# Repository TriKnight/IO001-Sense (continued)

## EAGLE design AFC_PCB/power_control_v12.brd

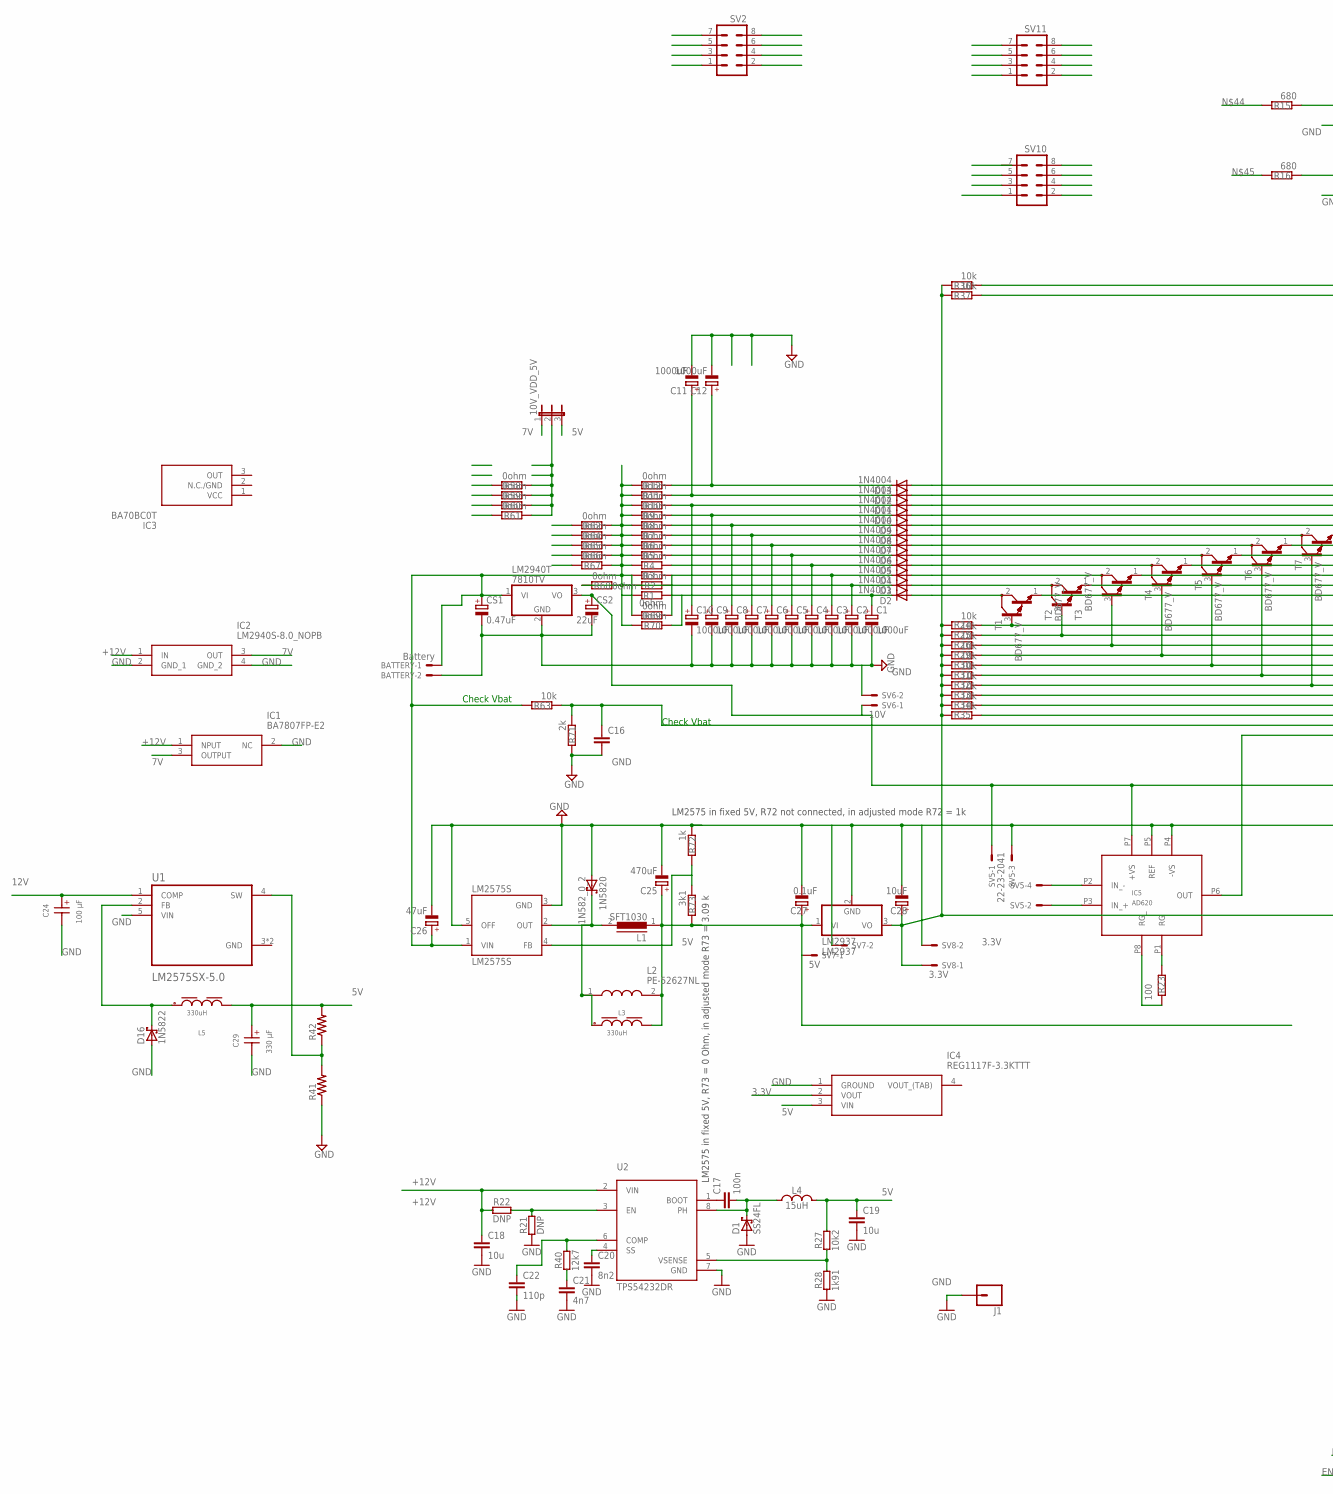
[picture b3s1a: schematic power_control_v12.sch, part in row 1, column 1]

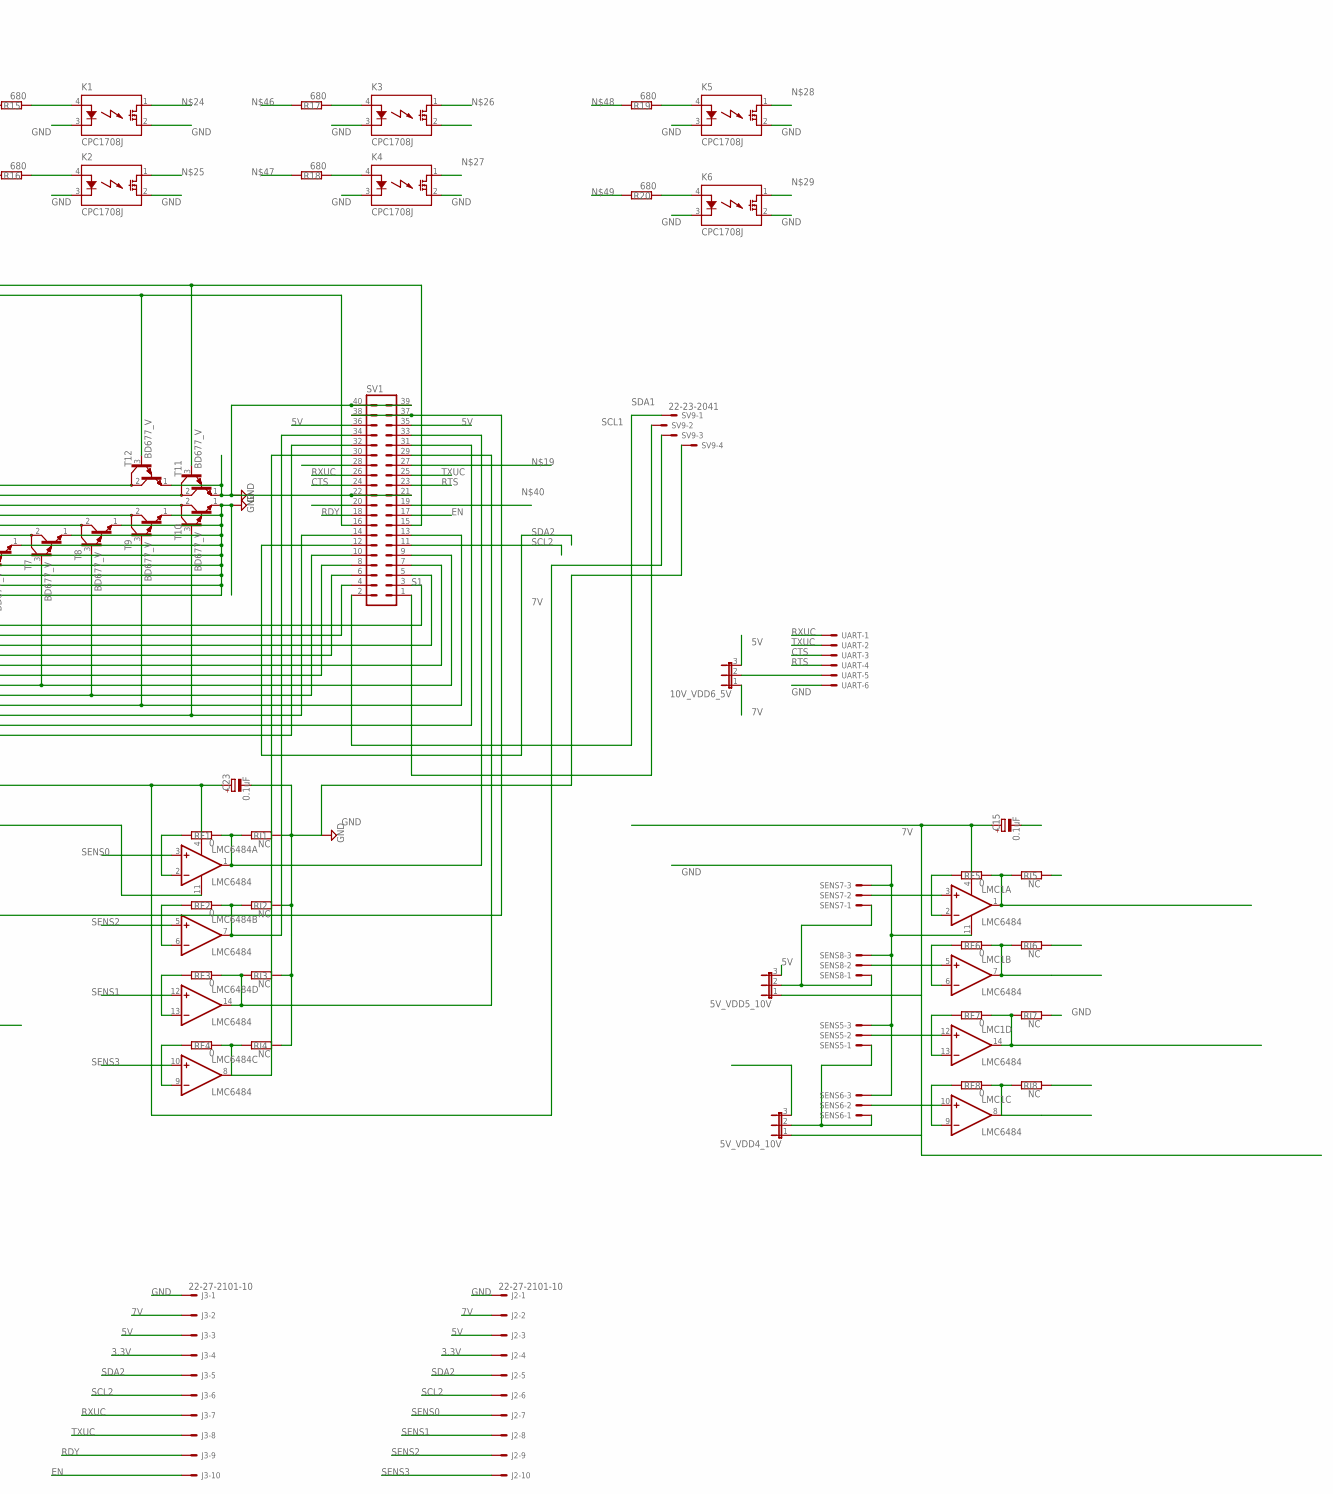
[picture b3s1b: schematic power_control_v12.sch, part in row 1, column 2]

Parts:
1N5820: 1N582_0_2; C4111-15
5V_VDD4_10V, 5V_VDD5_10V, 10V_VDD6_5V, 10V_VDD_5V: JP2E; JP2
BATTERY: Battery; 22-23-2021
C1, C2, C3, C4, C5, C6, C7, C8, C9, C10, C11, C12: 1000uF; E5-10,5
C15, C23, C27: 0.1uF; E1,8-4
C16: C-EUC0805K; C0805K
C17: 100n; 0402-1005X55N
C18, C19: 10u; 0603-1608X90N
C20: 8n2; 0402-1005X55N
C21: 4n7; 0402-1005X55N
C22: 110p; 0402-1005X55N
C24: 100 µF; WCAP-AS5H_10X10.5(DXL)
C25: 470uF; E3,5-8
C26: 47uF; E2-5
C28: 10uF; E1,8-4
C29: 330 µF; WCAP-AS5H_10X10.5(DXL)
CS1: 0.47uF; E2-5
CS2: 22uF; E2-5
D1: SS24FL; SOD123F
D2, D3: 1N4001; DO41-10
D4, D5, D6, D7, D8, D9, D10, D11, D12, D13: 1N4004; DO41-10
D16: 1N5822; C4111-15
IC1: BA7807FP-E2; BD33KA5FPE2
IC2: LM2940S-8.0_NOPB; KTT0003B
IC3: BA70BC0T; TO254P480X1010X2300-3P
IC4: REG1117F-3.3KTTT; TO254P1524X483-4N
IC5: AD620; DIL8
J1: CONN_01; 1X01
J2, J3: 22-27-2101-10; 6410-10
K1, K2, K3, K4, K5, K6: CPC1708J; I4-PAC
L1: SFT1030
L2: PE-52627NL; PE52629NL
L3, L5: 330uH; WE-PD_1280
L4: 15uH; SRN6045
LM2575S: LM2575S; TO263-5
LM2937: LM2937; TO263-3
LM2940T: 7810TV; TO220V
LMC1, LMC6484: LMC6484; DIL14
R1, R2, R3, R4, R5, R6, R7, R8, R9, R10, R11, R12: 0ohm; 0207/10
R15, R16, R17, R18, R19, R20: 680; M0805
R21, R22: DNP; 0402-1005X55N
R23: 100; R0805
R24, R25, R26, R29, R30, R31, R32, R33, R34, R35, R36, R37, R63: 10k; M0805
R27: 10k2; 0402-1005X55N
R28: 1k91; 0402-1005X55N
R40: 12k7; 0402-1005X55N
R41, R42: FLIPFLOP-RES; 0805-THM
R58, R59, R60, R61, R62, R64, R65, R66, R67, R68, R69, R70: 0ohm; M0805
R71: 2k; M0805
R72: 1k; M0805
R73: 3k1; M0805
RF1, RF3, RF4, RF5, RF7, RF8: 0; M0805
RF2, RF6: 0; R0805
RI1, RI2, RI3, RI4, RI5, RI6, RI7, RI8: NC; M0805
SENS5, SENS6, SENS7, SENS8: 22-23-2031
SV1: MA20-2
SV2, SV10, SV11: MA04-2
SV5, SV9: 22-23-2041
SV6: 10V; 22-23-2021
SV7: 5V; 22-23-2021
SV8: 3.3V; 22-23-2021
T1, T2, T3, T4, T5, T6, T7, T8, T9, T10, T11, T12: BD677_V; TO126V
U1: LM2575SX-5.0; VREG_TPS79625KTTR
U2: TPS54232DR; SO08
UART: 22-23-2061

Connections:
3.3V: C28.+, IC4.2 (VOUT), J2.4, J3.4, LM2937.3 (VO), R24.2, R25.2, R26.2, R29.2, R30.2, R31.2, R32.2, R33.2, R34.2, R35.2, R36.2, R37.2, SV1.37, SV1.38, SV8.1
5V: 5V_VDD4_10V.3, 5V_VDD5_10V.3, 10V_VDD6_5V.3, 10V_VDD_5V.3, C19.1, C25.+, C27.+, C29.1 (+), IC4.3 (VIN), J2.3, J3.3, L1.1, L2.2, L3.2, L4.2, L5.2, LM2937.1 (VI), R27.2, R42.2, R73.2, SV1.35, SV1.36, SV7.1
7V: 5V_VDD4_10V.1, 5V_VDD5_10V.1, 10V_VDD6_5V.1, 10V_VDD_5V.1, C15.+, C23.+, CS2.+, IC1.3 (OUTPUT), IC2.3 (OUT), IC5.P7 (+VS), J2.2, J3.2, LM2940T.3 (VO), LMC1.4 (V+), LMC6484.4 (V+), SV5.1, SV6.1, SV9.3
12V: C24.1 (+), U1.1 (COMP)
+12V: BATTERY.1, C18.1, C26.+, CS1.+, IC1.1 (NPUT), IC2.1 (IN), LM2575S.1 (VIN), LM2940T.1 (VI), R1.2, R2.2, R3.2, R4.2, R5.2, R6.2, R7.2, R8.2, R9.2, R10.2, R11.2, R12.2, R22.1, R62.1, R63.2, R64.1, R65.1, R66.1, R67.1, R68.1, R69.2, R70.2, U2.2 (VIN)
CTS: SV1.24, UART.3
EN: J3.10, SV1.17
GND: 1N5820.A, BATTERY.2, C1.-, C2.-, C3.-, C4.-, C5.-, C6.-, C7.-, C8.-, C9.-, C10.-, C11.-, C12.-, C15.-, C16.2, C18.2, C19.2, C20.2, C21.2, C22.2, C23.-, C24.2 (-), C25.-, C26.-, C27.-, C28.-, C29.2 (-), CS1.-, CS2.-, D1.A, D16.A, IC1.2 (NC), IC2.2 (GND_1), IC2.4 (GND_2), IC4.1 (GROUND), IC5.P4 (-VS), IC5.P5 (REF), J1.1, J2.1, J3.1, K1.2 (DS2), K1.3 (K), K2.2 (DS2), K2.3 (K), K3.2 (DS2), K3.3 (K), K4.2 (DS2), K4.3 (K), K5.2 (DS2), K5.3 (K), K6.2 (DS2), K6.3 (K), LM2575S.3 (GND), LM2575S.5 (OFF), LM2937.2 (GND), LM2940T.2 (GND), LMC1.11 (V-), LMC6484.11 (V-), R21.1, R28.1, R41.1, R71.2, R72.1, RI1.1, RI2.1, RI3.1, RI4.1, RI5.1, RI6.1, RI7.1, RI8.1, SENS5.3, SENS6.3, SENS7.3, SENS8.3, SV1.21, SV1.22, SV1.39, SV1.40, SV5.3, SV6.2, SV7.2, SV8.2, SV9.4, T1.1 (E), T2.1 (E), T3.1 (E), T4.1 (E), T5.1 (E), T6.1 (E), T7.1 (E), T8.1 (E), T9.1 (E), T10.1 (E), T11.1 (E), T12.1 (E), U1.3 (GND), U1.5 (VIN), U1.6 (GND), U2.7 (GND), UART.6
unnamed: C1.+, D2.C, R1.1, R70.1, SV2.1
unnamed: D2.A, SV2.2, T1.2 (C)
unnamed: C2.+, D3.C, R2.1, R68.2, SV2.3
unnamed: C3.+, D4.C, R3.1, R69.1, SV2.5
unnamed: C4.+, D5.C, R4.1, R67.2, SV2.7
unnamed: C5.+, D6.C, R5.1, R66.2, SV10.1
unnamed: C6.+, D7.C, R6.1, R65.2, SV10.3
unnamed: C7.+, D8.C, R7.1, R64.2, SV10.5
unnamed: C8.+, D9.C, R8.1, R62.2, SV10.7
unnamed: C9.+, D10.C, R9.1, R61.2, SV11.1
unnamed: C10.+, D11.C, R10.1, R60.2, SV11.3
unnamed: C11.+, D12.C, R11.1, R59.2, SV11.5
unnamed: C12.+, D13.C, R12.1, R58.2, SV11.7
unnamed: 5V_VDD4_10V.2, SENS5.1, SENS6.1
unnamed: LMC1.3 (+IN), SENS7.2
unnamed: LMC1.2 (-IN), RF5.2
unnamed: LMC1.1 (OUT), RF5.1, RI5.2, SV1.27
unnamed: 10V_VDD6_5V.2, UART.5
unnamed: LMC1.5 (+IN), SENS8.2
unnamed: LM2575S.4 (FB), R72.2, R73.1
unnamed: R36.1, SV1.15, T11.3 (B)
unnamed: D3.A, K1.1 (DS1), SV2.4, T2.2 (C)
unnamed: D4.A, K2.1 (DS1), SV2.6, T3.2 (C)
unnamed: D5.A, K3.1 (DS1), SV2.8, T4.2 (C)
unnamed: D6.A, K4.1 (DS1), SV10.2, T5.2 (C)
unnamed: D7.A, K5.1 (DS1), SV10.4, T6.2 (C)
unnamed: D8.A, K6.1 (DS1), SV10.6, T7.2 (C)
unnamed: D9.A, SV10.8, T8.2 (C)
unnamed: D10.A, SV11.2, T9.2 (C)
unnamed: D11.A, SV11.4, T10.2 (C)
unnamed: D12.A, SV11.6, T11.2 (C)
unnamed: D13.A, SV11.8, T12.2 (C)
unnamed: LMC1.6 (-IN), RF6.2
unnamed: LMC1.7 (OUT), RF6.1, RI6.2, SV1.28
unnamed: LMC1.13 (-IN), RF7.2
unnamed: LMC1.9 (-IN), RF8.2
unnamed: LMC1.12 (+IN), SENS5.2
unnamed: LMC1.14 (OUT), RF7.1, RI7.2, SV1.19
unnamed: R15.2, R25.1, SV1.4, T2.3 (B)
unnamed: R16.2, R26.1, SV1.5, T3.3 (B)
unnamed: R17.2, R29.1, SV1.6, T4.3 (B)
unnamed: R18.2, R30.1, SV1.7, T5.3 (B)
unnamed: R19.2, R31.1, SV1.8, T6.3 (B)
unnamed: R20.2, R32.1, SV1.9, T7.3 (B)
unnamed: R33.1, SV1.10, T8.3 (B)
unnamed: R34.1, SV1.13, T9.3 (B)
unnamed: R35.1, SV1.14, T10.3 (B)
unnamed: LMC1.10 (+IN), SENS6.2
unnamed: LMC1.8 (OUT), RF8.1, RI8.2, SV1.20
unnamed: K1.4 (A), R15.1
unnamed: K2.4 (A), R16.1
unnamed: 5V_VDD5_10V.2, SENS7.1, SENS8.1
unnamed: K3.4 (A), R17.1
unnamed: R37.1, SV1.16, T12.3 (B)
unnamed: K5.4 (A), R19.1
unnamed: R21.2, R22.2, U2.3 (EN)
unnamed: IC5.P2 (IN_-), SV5.4
unnamed: IC5.P3 (IN_+), SV5.2
unnamed: 1N5820.C, L1.2, L2.1, L3.1, LM2575S.2 (OUT)
unnamed: LMC6484.8 (OUT), RF4.1, RI4.2, SV1.30
unnamed: K6.4 (A), R20.1
unnamed: K4.4 (A), R18.1
unnamed: IC5.P1 (RG), R23.2
unnamed: C17.1, U2.1 (BOOT)
unnamed: C17.2, D1.C, L4.1, U2.8 (PH)
unnamed: IC5.P8 (RG_), R23.1
unnamed: IC5.P6 (OUT), SV1.32
unnamed: R27.1, R28.2, U2.5 (VSENSE)
unnamed: C20.1, U2.4 (SS)
unnamed: LMC6484.2 (-IN), RF1.2
unnamed: 10V_VDD_5V.2, R58.1, R59.1, R60.1, R61.1
unnamed: LMC6484.1 (OUT), RF1.1, RI1.2, SV1.33
unnamed: C16.1, R63.1, R71.1, SV1.31
unnamed: LMC6484.6 (-IN), RF2.2
unnamed: LMC6484.7 (OUT), RF2.1, RI2.2, SV1.34
unnamed: LMC6484.13 (-IN), RF3.2
unnamed: C22.1, R40.2, U2.6 (COMP)
unnamed: LMC6484.14 (OUT), RF3.1, RI3.2, SV1.29
unnamed: LMC6484.9 (-IN), RF4.2
unnamed: C21.1, R40.1
unnamed: D16.C, L5.1, U1.2 (FB)
unnamed: R41.2, R42.1, U1.4 (SW)
RDY: J3.9, SV1.18
RTS: SV1.23, UART.4
RXUC: J3.7, SV1.26, UART.1
S1: R24.1, SV1.3, T1.3 (B)
SCL1: SV1.1, SV9.2
SCL2: J2.6, J3.6, SV1.11
SDA1: SV1.2, SV9.1
SDA2: J2.5, J3.5, SV1.12
SENS0: J2.7, LMC6484.3 (+IN)
SENS1: J2.8, LMC6484.12 (+IN)
SENS2: J2.9, LMC6484.5 (+IN)
SENS3: J2.10, LMC6484.10 (+IN)
TXUC: J3.8, SV1.25, UART.2

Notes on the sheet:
Check Vbat
LM2575 in fixed 5V, R72 not connected, in adjusted mode R72 = 1k
LM2575 in fixed 5V, R73 = 0 Ohm, in adjusted mode R73 = 3.09 k

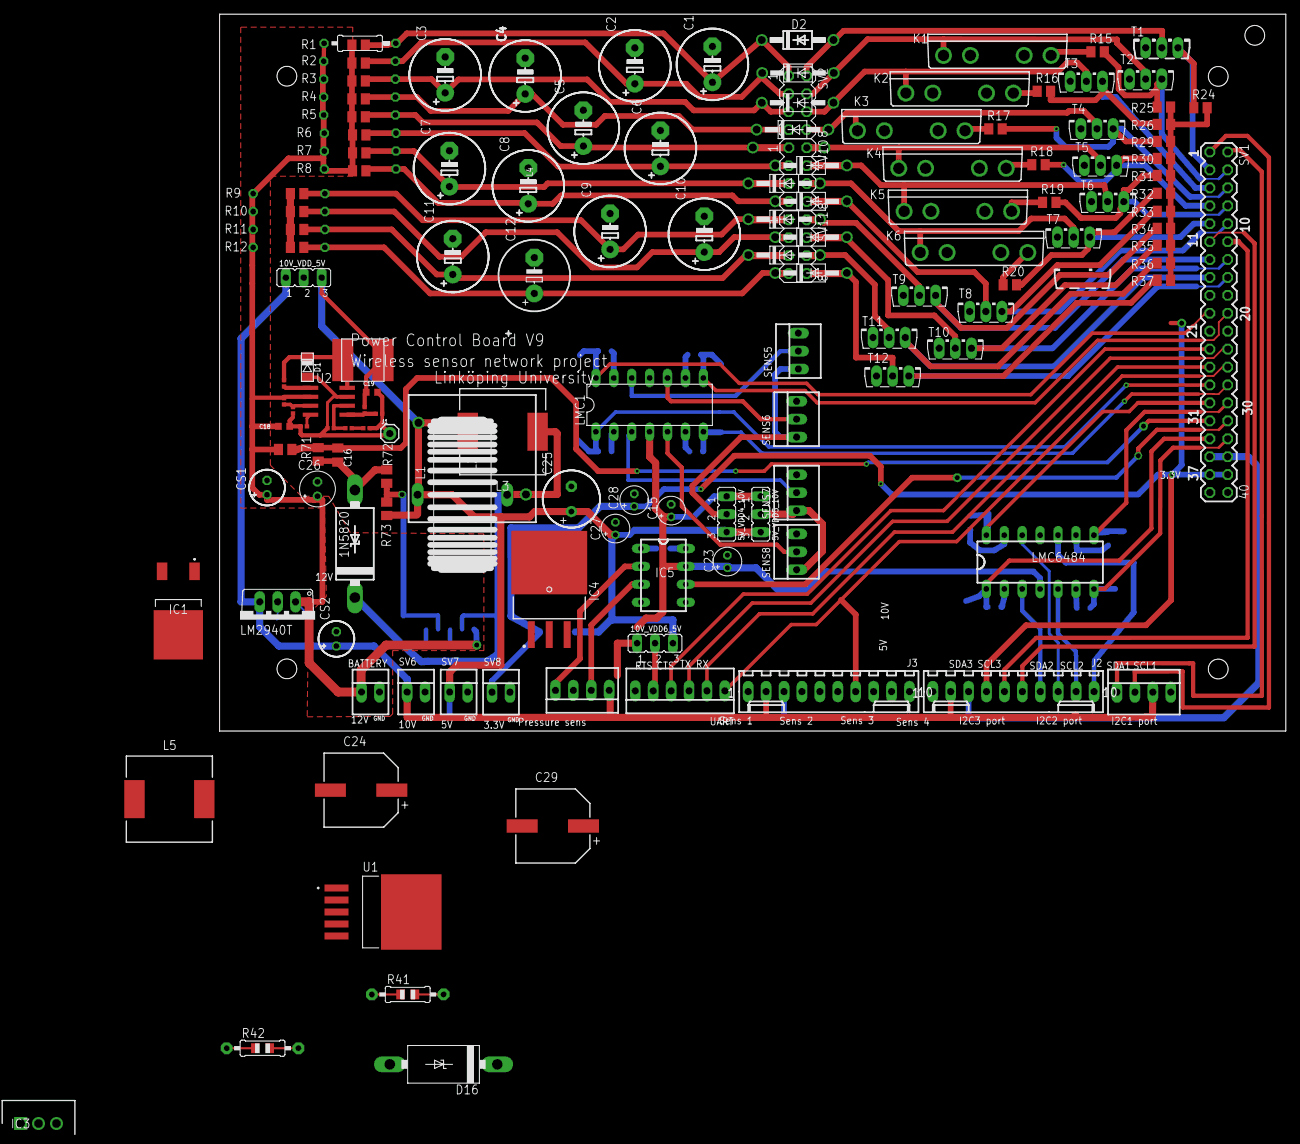
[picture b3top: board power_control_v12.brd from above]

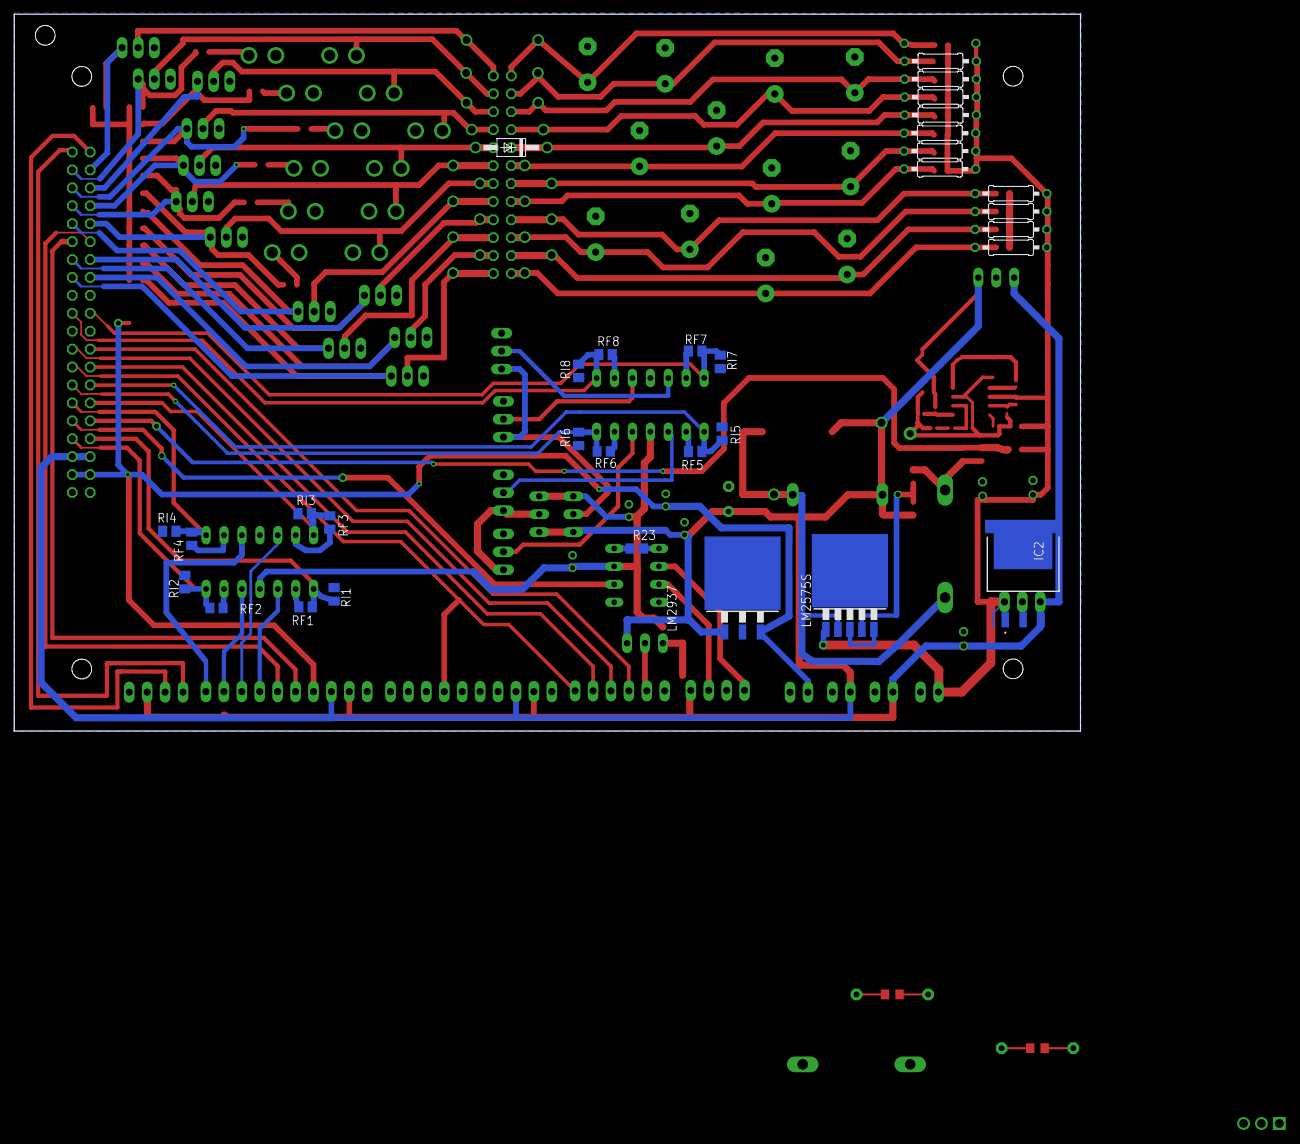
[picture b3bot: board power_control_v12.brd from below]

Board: 2 copper layers, 151.1 x 101.6 mm, 171 parts (32 on the bottom side), 103 nets.

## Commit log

2020-01-16 The MCUCode v.10
2020-02-12 update Module Sim
2020-02-13 Update Baseboard with logging 1 minute
2020-02-15 This change the logging time to 10 min
2023-10-10 Add AFC PCB and code IoT
